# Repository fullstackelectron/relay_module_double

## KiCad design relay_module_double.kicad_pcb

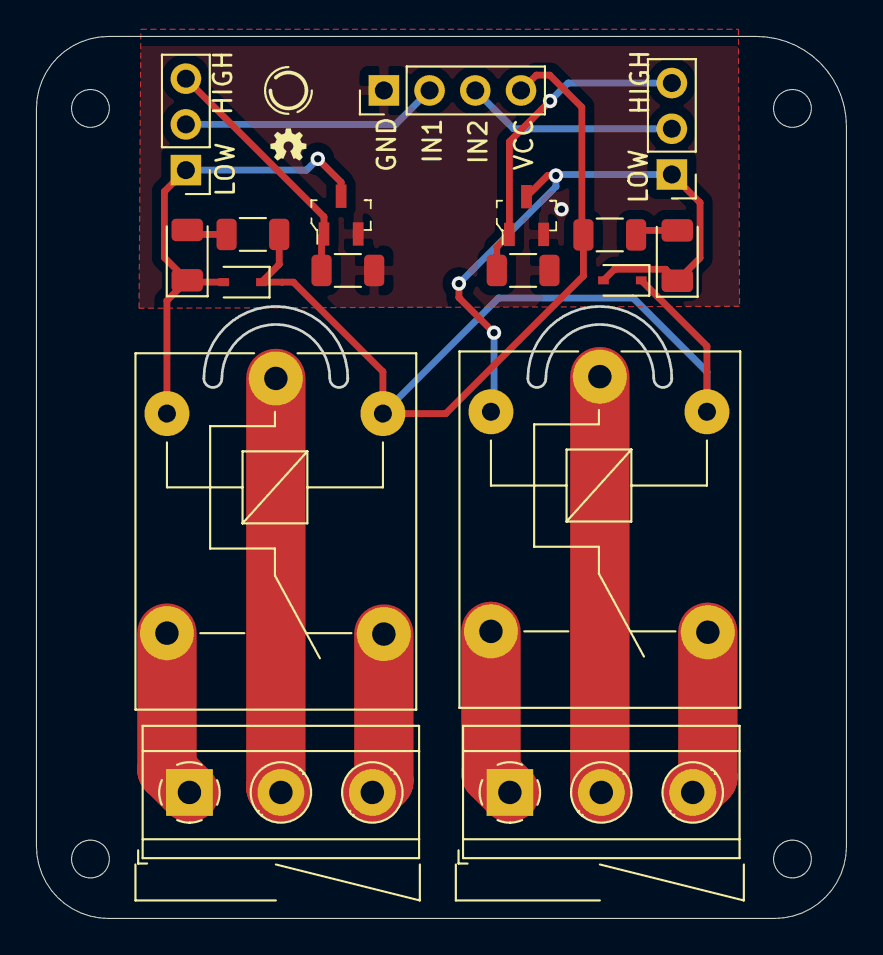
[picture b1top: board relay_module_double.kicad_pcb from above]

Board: 2 copper layers, 44.9 x 48.9 mm, 17 parts (0 on the bottom side), 16 nets.

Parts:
D1, D4: LED; LED_1206_3216Metric
D2, D3: D; D_SOD-323
J1: Conn_01x04; PinHeader_1x04_P2.54mm_Vertical
J2, J3: Conn_01x03_Female; TerminalBlock_Phoenix_MKDSN-1,5-3-5.08_1x03_P5.08mm_Horizon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
J4: high_low_1; PinHeader_1x03_P2.54mm_Vertical
J5: high_low_2; PinHeader_1x03_P2.54mm_Vertical
K1, K2: SANYOU_SRD_Form_C; Relay_SPDT_SANYOU_SRD_Series_Form_C
Q1, Q2: MMBT7002; SOT-23-3
R1, R3: 10k; R_1206_3216Metric
R2, R4: 220; R_1206_3216Metric

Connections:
CMN: J2.2, K1.1
CMN2: J3.2, K2.1
COIL1: D1.1, D3.2, J4.1, K1.2, Q1.3
COIL1_2: D2.2, D4.1, J5.1, K2.2, Q2.3
COIL2: D2.1, D3.1, J1.4, K1.5, K2.5, R2.1, R4.1
GND: J1.1, Q1.2, Q2.2, R1.1, R3.1
IN1: J1.2, J4.2
IN2: J1.3, J5.2
NC: J2.3, K1.4
NC2: J3.3, K2.4
NO: J2.1, K1.3
NO2: J3.1, K2.3
unnamed: D1.2, R2.2
unnamed: D4.2, R4.2
unnamed: J4.3, Q1.1, R1.2
unnamed: J5.3, Q2.1, R3.2

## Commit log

2021-02-09 Version 1.0 - HIGH/LOW capabilities - small signal required
